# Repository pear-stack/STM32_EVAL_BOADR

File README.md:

# STM32_EVAL_BOARD
Simple STM32 Hardware Design

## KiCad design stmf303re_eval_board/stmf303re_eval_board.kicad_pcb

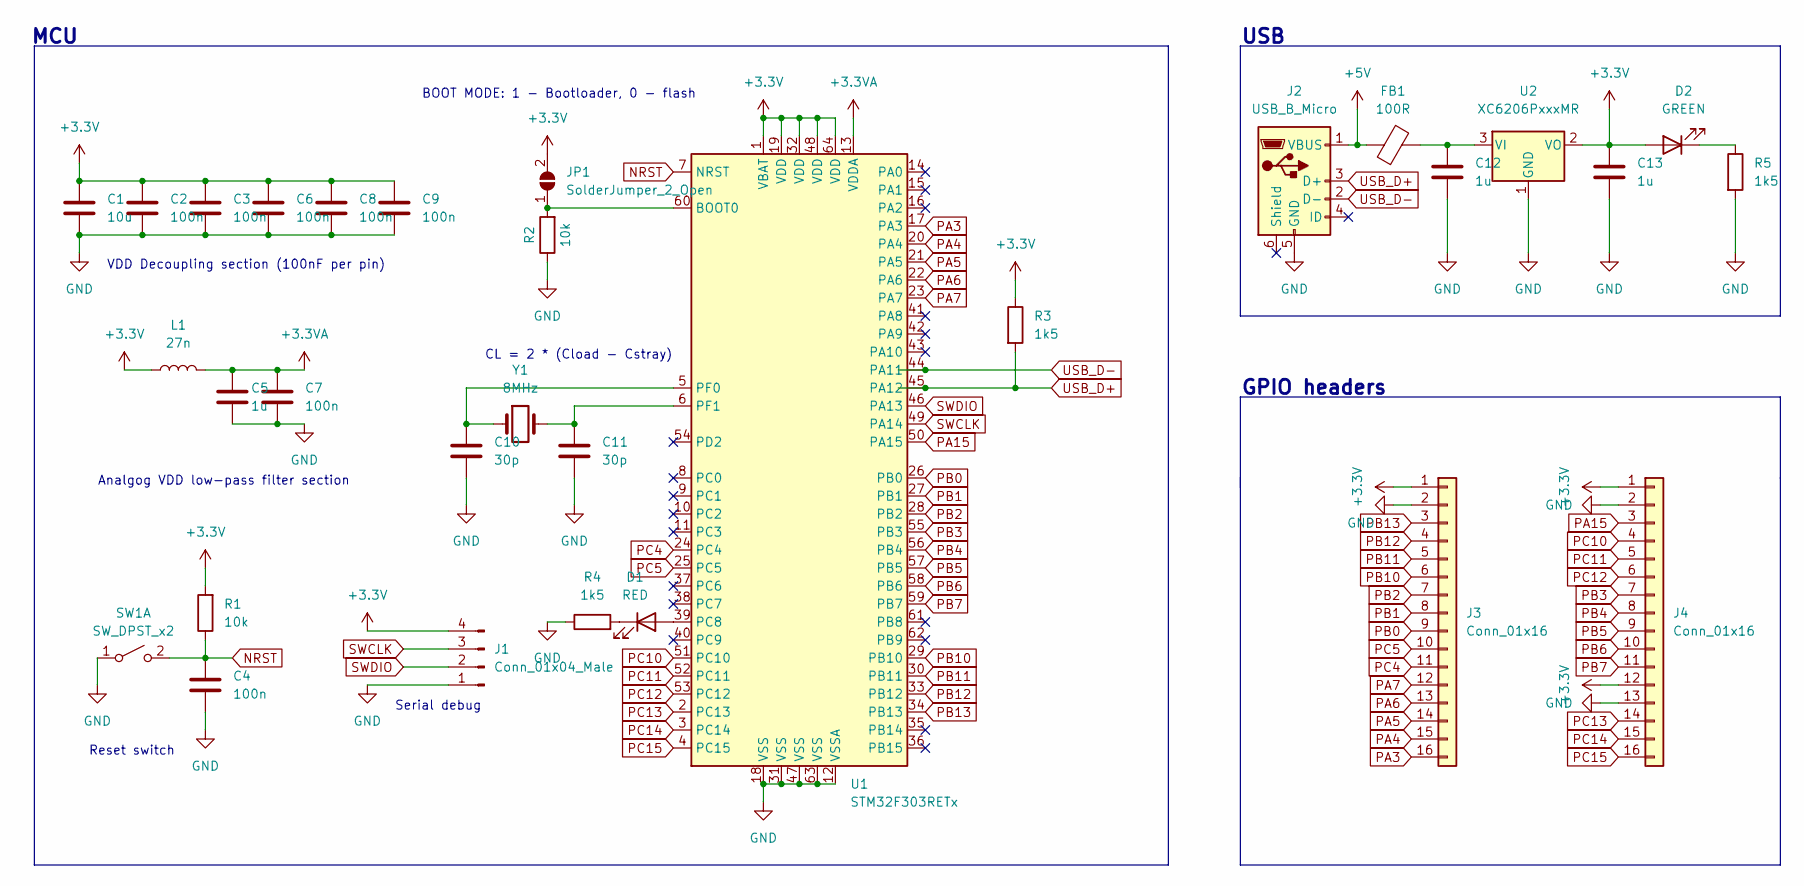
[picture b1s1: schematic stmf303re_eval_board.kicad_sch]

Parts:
C1: 10u; C_0603_1608Metric
C2, C3, C4, C6, C7, C8, C9: 100n; C_0402_1005Metric
C5, C12, C13: 1u; C_0603_1608Metric
C10, C11: 30p; C_0402_1005Metric
D1: RED; LED_0805_2012Metric
D2: GREEN; LED_0805_2012Metric
FB1: 100R; L_0805_2012Metric
J1: Conn_01x04_Male; PinHeader_1x04_P2.54mm_Vertical
J2: USB_B_Micro; USB_Micro-B_Molex_47346-0001
J3, J4: Conn_01x16; PinSocket_1x16_P2.54mm_Vertical
JP1: SolderJumper_2_Open; SolderJumper-2_P1.3mm_Open_RoundedPad1.0x1.5mm
L1: 27n; L_0402_1005Metric
R1, R2: 10k; R_0603_1608Metric
R3, R4, R5: 1k5; R_0603_1608Metric
SW1: SW_DPST_x2; SW_SPST_CK_RS282G05A3
U1: STM32F303RETx; LQFP-64_10x10mm_P0.5mm
U2: XC6206PxxxMR; SOT-23
Y1: 8MHz; Crystal_SMD_0603-2Pin_6.0x3.5mm

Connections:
+3.3V: C1.1, C2.1, C3.1, C6.1, C8.1, C9.1, C13.1, D2.2 (A), J1.4, J3.1, J4.1, J4.12, JP1.2 (B), L1.1, R1.2, R3.1, U1.1 (VBAT), U1.19 (VDD), U1.32 (VDD), U1.48 (VDD), U1.64 (VDD), U2.2 (VO)
+3.3VA: C5.1, C7.1, L1.2, U1.13 (VDDA)
+5V: FB1.1, J2.1 (VBUS)
GND: C1.2, C2.2, C3.2, C4.2, C5.2, C6.2, C7.2, C8.2, C9.2, C10.2, C11.2, C12.2, C13.2, J1.1, J2.5 (GND), J3.2, J4.2, J4.13, R2.1, R4.1, R5.2, SW1.1 (A), U1.12 (VSSA), U1.18 (VSS), U1.31 (VSS), U1.47 (VSS), U1.63 (VSS), U2.1 (GND)
NRST: C4.1, R1.1, SW1.2 (B), U1.7 (NRST)
unnamed: C10.1, U1.5 (PF0), Y1.1
unnamed: C11.1, U1.6 (PF1), Y1.2
unnamed: C12.1, FB1.2, U2.3 (VI)
unnamed: D1.1 (K), R4.2
unnamed: D1.2 (A), U1.39 (PC8)
unnamed: D2.1 (K), R5.1
unnamed: JP1.1 (A), R2.2, U1.60 (BOOT0)
PA3: J3.16, U1.17 (PA3)
PA4: J3.15, U1.20 (PA4)
PA5: J3.14, U1.21 (PA5)
PA6: J3.13, U1.22 (PA6)
PA7: J3.12, U1.23 (PA7)
PA15: J4.3, U1.50 (PA15)
PB0: J3.9, U1.26 (PB0)
PB1: J3.8, U1.27 (PB1)
PB2: J3.7, U1.28 (PB2)
PB3: J4.7, U1.55 (PB3)
PB4: J4.8, U1.56 (PB4)
PB5: J4.9, U1.57 (PB5)
PB6: J4.10, U1.58 (PB6)
PB7: J4.11, U1.59 (PB7)
PB10: J3.6, U1.29 (PB10)
PB11: J3.5, U1.30 (PB11)
PB12: J3.4, U1.33 (PB12)
PB13: J3.3, U1.34 (PB13)
PC4: J3.11, U1.24 (PC4)
PC5: J3.10, U1.25 (PC5)
PC10: J4.4, U1.51 (PC10)
PC11: J4.5, U1.52 (PC11)
PC12: J4.6, U1.53 (PC12)
PC13: J4.14, U1.2 (PC13)
PC14: J4.15, U1.3 (PC14)
PC15: J4.16, U1.4 (PC15)
SWCLK: J1.3, U1.49 (PA14)
SWDIO: J1.2, U1.46 (PA13)
USB_D+: J2.3 (D+), R3.2, U1.45 (PA12)
USB_D-: J2.2 (D-), U1.44 (PA11)

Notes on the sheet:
USB
Reset switch
Serial debug
GPIO headers
CL = 2 * (Cload - Cstray)
BOOT MODE: 1 - Bootloader, 0 - flash
Analgog VDD low-pass filter section
MCU
VDD Decoupling section (100nF per pin)

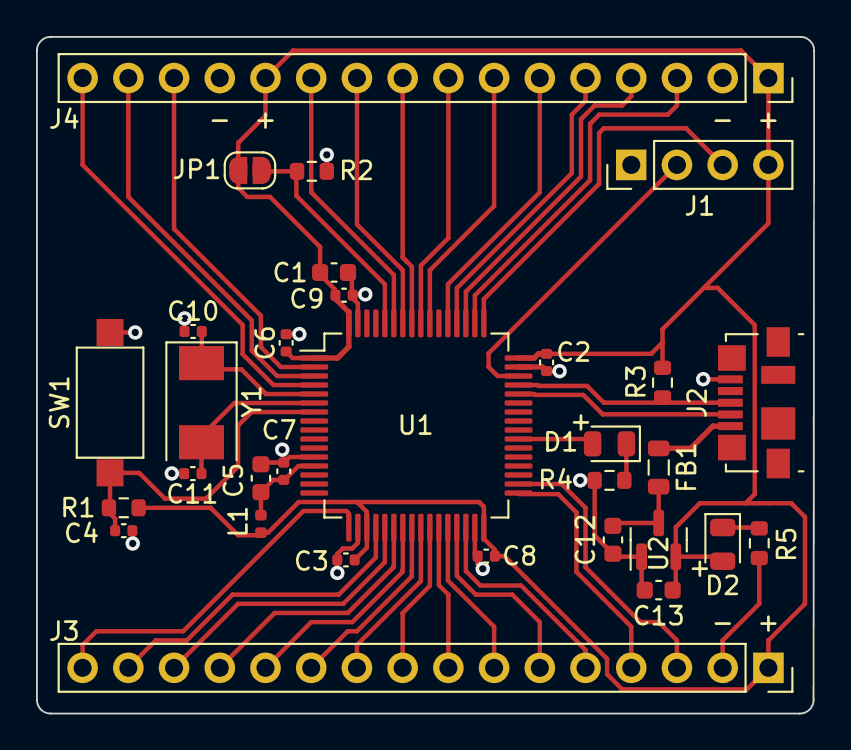
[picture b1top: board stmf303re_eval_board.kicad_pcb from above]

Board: 2 copper layers, 43.2 x 37.6 mm, 31 parts (0 on the bottom side), 42 nets.

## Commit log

2022-10-21 init commit
2022-10-21 basic scheme, footprint and layout
2022-11-24 usb, traces fixed
2022-11-25 traces update
